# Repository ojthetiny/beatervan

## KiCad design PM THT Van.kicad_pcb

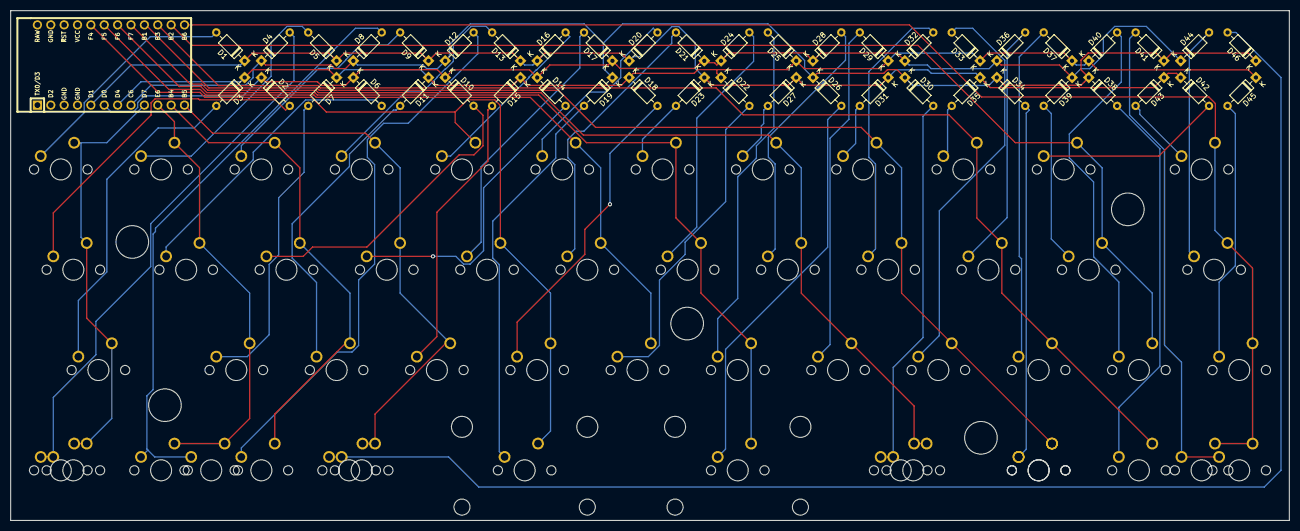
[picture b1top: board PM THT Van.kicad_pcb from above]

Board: 2 copper layers, 242.9 x 96.8 mm, 99 parts (0 on the bottom side), 61 nets.

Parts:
D1, D2, D3, D4, D5, D6, D7, D8, D9, D10, D11, D12, D13, D14, D15, D16, D17, D18, D19, D20, D21, D22, D23, D24, D25, D26, D27, D28, D29, D30, D31, D32, D33, D34, D35, D36, D37, D38, D39, D40, D41, D42, D43, D44, D45, D46: 1N4148; D_DO-35_SOD27_P7.62mm_Horizontal
SW1, SW5, SW6, SW7, SW9, SW10, SW11, SW13, SW14, SW15, SW16, SW17, SW18, SW20, SW21, SW22, SW23, SW24, SW25, SW27, SW28, SW29, SW32, SW33, SW34, SW36, SW37, SW38, SW39, SW41, SW42, SW43, SW44, SW45, SW48, SW50, SW51, SW52, SW53: MX_LED; MXOnly-1U-NoLED
SW2, SW4, SW12, SW30: MX_LED; MXOnly-1.25U-NoLED
SW3, SW40, SW46: MX_LED; MXOnly-1.75U-NoLED
SW8, SW31, SW35, SW47: MX_LED; MXOnly-1.5U-NoLED
SW19: MX_LED; MXOnly-2.25U-ReversedStabilizers-NoLED
SW26: MX_LED; MXOnly-2U-ReversedStabilizers-NoLED
U1: ProMicro; ArduinoProMicro

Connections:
COL0: SW1.2, SW2.2, SW3.2, SW4.2, SW50.2, U1.9
COL1: SW5.2, SW6.2, SW7.2, SW8.2, SW51.2, U1.10
COL2: SW9.2, SW10.2, SW11.2, SW52.2, U1.11
COL3: SW12.2, SW13.2, SW14.2, SW15.2, SW53.2, U1.12
COL4: SW16.2, SW17.2, SW18.2, SW19.2, U1.20
COL5: SW20.2, SW21.2, SW22.2, U1.19
COL6: SW23.2, SW24.2, SW25.2, SW26.2, U1.18
COL7: SW27.2, SW28.2, SW29.2, SW30.2, SW31.2, U1.17
COL8: SW32.2, SW33.2, SW34.2, SW35.2, SW36.2, U1.16
COL9: SW37.2, SW38.2, SW39.2, SW41.2, U1.15
COL10: SW42.2, SW43.2, SW45.2, U1.14
COL11: SW40.2, SW44.2, SW46.2, SW47.2, SW48.2, U1.13
unnamed: D1.2, SW1.1
unnamed: D2.2, SW2.1
unnamed: D3.2, SW3.1
unnamed: D4.2, SW4.1, SW50.1
unnamed: D5.2, SW5.1
unnamed: D6.2, SW6.1
unnamed: D7.2, SW7.1
unnamed: D8.2, SW8.1, SW51.1
unnamed: D9.2, SW9.1
unnamed: D10.2, SW10.1
unnamed: D11.2, SW11.1
unnamed: D12.2, SW52.1
unnamed: D13.2, SW13.1
unnamed: D14.2, SW14.1
unnamed: D15.2, SW15.1
unnamed: D16.2, SW16.1
unnamed: D17.2, SW17.1
unnamed: D18.2, SW18.1
unnamed: D19.2, SW19.1
unnamed: D20.2, SW20.1
unnamed: D21.2, SW21.1
unnamed: D22.2, SW22.1
unnamed: D23.2, SW23.1
unnamed: D24.2, SW24.1
unnamed: D25.2, SW25.1
unnamed: D26.2, SW26.1
unnamed: D27.2, SW27.1
unnamed: D28.2, SW28.1
unnamed: D29.2, SW29.1
unnamed: D30.2, SW30.1, SW31.1
unnamed: D31.2, SW32.1
unnamed: D32.2, SW33.1
unnamed: D33.2, SW34.1
unnamed: D34.2, SW35.1, SW36.1
unnamed: D35.2, SW37.1
unnamed: D36.2, SW38.1
unnamed: D37.2, SW39.1
unnamed: D38.2, SW41.1
unnamed: D39.2, SW42.1
unnamed: D40.2, SW43.1
unnamed: D41.2, SW40.1, SW44.1
unnamed: D42.2, SW45.1
unnamed: D43.2, SW46.1
unnamed: D44.2, SW47.1
unnamed: D45.2, SW48.1
ROW0: D1.1, D5.1, D9.1, D13.1, D16.1, D20.1, D23.1, D27.1, D31.1, D35.1, D42.1, D43.1, U1.5
ROW1: D2.1, D6.1, D10.1, D14.1, D17.1, D21.1, D24.1, D28.1, D32.1, D36.1, D39.1, D44.1, U1.6
ROW2: D3.1, D7.1, D11.1, D15.1, D18.1, D22.1, D25.1, D29.1, D33.1, D37.1, D40.1, D45.1, U1.7
ROW3: D4.1, D8.1, D12.1, D19.1, D26.1, D30.1, D34.1, D38.1, D41.1, D46.1, U1.8
